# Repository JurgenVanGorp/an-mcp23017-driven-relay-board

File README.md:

Guide creation date: 13-Nov-2021

# An MCP23017 driven relay board for Home Assistant on a Raspberry Pi
A schematic and hardware board for an MCP23017 multi-I/O controller driven relays.

Previous topic: [Step 4: Controlling the MCP23017 from within Home-Assistant.](https://github.com/JurgenVanGorp/MCP23017-multi-I-O-Control-with-Raspberry-Pi-and-Home-Assistant)

## Introduction

In the previous topics it was shown how an MCP23017 can be used for controlling toggle relays with an MCP23017 multi-I/O chip. The examples made use of an MCP23017 chip on a breadboard. For real life usage we will need a PCB that can be properly installed in a rack.

This guide describes a simple PCB board in Eurocard format (10cm x 16cm) that allows connecting an MCP23017 to a Raspberry Pi with Home Assistant, over the I2C bus. The board has 15 open ended relays. The 16th output is used to drive an "identification" LED. It can be used to identify the board if you are using multiple boards, and for verification that the communication is working properly.

The board needs a 12V power supply. The 12V is converted to 5V on the board, and is also used to power the mini relays. With some modifications you can also use the board with 5V directly, but you would need to replace the relays with pin-compatible 5V relays. I am using 12V for the simple reason that all switches in my house operate on 12V. The translation to higher voltages is only done in the power box.

**WARNING** Even though the PCB board described below does provide you with physical segregation with relays, IT IS NOT SUITED FOR HIGH VOLTAGE OR HIGH CURRENT USE. The low voltage and high voltage lines on the PCB are not sufficiently separated on the PCB for safe use with high voltages. The board can be used with low-voltage (max 48V) toggle relays (aka teleruptors) at a maximum of 500 milliAmps.

## Using and changing the files in this repository

I have created the schematic and PCB in this repository with the open and free [KiCad EDA](https://www.kicad.org/) software. I cannot express enough how much I am grateful to [the developers](https://www.kicad.org/about/kicad/) of this PCB software. As far as I'm concerned the times of too-expensive PCB software are over.

The PCB file looks as follows.

The GERBER PCB Files are included in the package, so you don't need to compile these for yourself.

There are many companies that will be able to create the PCB files for you. My personal favorite is [Eurocircuits.eu](https://www.eurocircuits.com/), but that's a personal choice of course. You can also create your own PCBs; the PDF file is added in the repository. But let's be honest, ordering the PCB looks a lot more professional and will last longer.

**INFO** In honnesty: the image above does not fully match the PCB you can find in the repository. In this prototype I made use of RJ10 connectors for the I2C connections, but these connectors are difficult to find. If you find one, it will probably have a slightly footprint. For that reason I used 'standard' 3-pin connectors in the final PCB layout.

## Components used.

This is the list of components used, and where I have found them.

| Quantity | Component    | Value                     | Source                 | ~cost/Piece   |
|:--------:|--------------|--------------------------:|------------------------|--------------:|
| 1        | PCB Board    | See Gerber files | [eurocircuits.eu](https://www.eurocircuits.eu) | € 35.00 | 
| 1        | IC           | MCP23017                  | [mouser.com](https://eu.mouser.com/ProductDetail/Microchip/MCP23017-E-SP?qs=sGAEpiMZZMsVgcksf1EMUq%252Bl%252ByrW%252Br2s) | € 1.35 |
| 2        | 14 pins socket | MCP23017                  | [mouser.com](https://www.conrad.com/p/tru-components-ic-socket-contact-spacing-254-mm-762-mm-number-of-pins-14-1-pcs-1568704) | € 0.40 |
| 2        | Resistor     | 470 |  |  | 
| 16       | Diode        | 1N4007 | [conrad.com](https://www.conrad.com/p/diotec-si-rectifier-1n4007-do-204al-1000-v-1-a-162272) | € 0.09 | 
| 15       | Resistor     | 4K7 | [conrad.com](https://www.conrad.com/p/tru-components-tc-mf0w4ff4701a50203-metal-film-resistor-47-k-axial-lead-0207-025-w-1-1-pcs-1585059) | € 0.10 | 
| 1        | Capacitor    | 22nF  | [conrad.com](https://www.conrad.com/p/tru-components-tc-k22nf5-ceramic-capacitor-tht-22-nf-100-v-20-1-pcs-1589451) | € 0.10 | 
| 3        | Capacitor    | 220nF | [conrad.com](https://www.conrad.com/p/kemet-c320c224m5u5ta-ceramic-capacitor-radial-lead-220-nf-50-v-20-l-x-w-x-h-508-x-318-x-584-mm-1-pcs-1420328) | € 0.60 | 
| 2        | Capacitor     | 220uF | [conrad.com](https://www.conrad.com/p/europe-chemicon-eky-500ell221mj16s-electrolytic-capacitor-radial-lead-5-mm-220-f-50-v-20-x-h-10-mm-x-16-mm-1-pc-1505568) | € 0.50 | 
| 15       | Transistor   | BC547 **(1)** | [conrad.com](https://www.conrad.com/search?search=140539&searchType=regular) | € 0.05 |
| 1        | 12V to 5V DC | OKI-78SR-5_1.5-W36H-C **(2)** | [mouser.com](https://eu.mouser.com/ProductDetail/Murata/OKI-78SR-5-15-W36H-C?qs=sGAEpiMZZMsbRVlHDoeFZD%252BySXGErvIJc3su7QBo1Is%3D) | € 3.64 | 
| 15       | Relay 12V    | G5V-1-DC12 **(3)**           | [mouser.com](https://eu.mouser.com/ProductDetail/Omron/G5V-1-DC12?qs=sGAEpiMZZMv0NwlthflBi%2Fae0vpIDW5L) | € 1.45 |
| 3        | Jumper       | N/A      | e.g. [conrad.com](https://www.conrad.com/p/tru-components-shorting-jumper-contact-spacing-254-mm-pins-per-row2-content-100-pcs-1693950) | € 0.35 | 
| 1        | Connector 1x2 | DG350-3.5-03P    | [conrad.com](https://www.conrad.com/p/degson-dg350-35-02p-14-00ah-200-screw-terminal-2-mm-number-of-pins-2-green-200-pcs-1595136) | € 0.22 | 
| 2        | Connector 1x3 | DG350-3.5-02P    | [conrad.com](https://www.conrad.com/p/degson-dg350-35-03p-14-00ah-200-screw-terminal-2-mm-number-of-pins-3-green-200-pcs-1595217) | € 0.32 | 
| 5        | 1x6 Spring connector | PTR 54191060051E | [conrad.com](https://www.conrad.com/p/ptr-54191060051e-spring-loaded-terminal-075-mm-number-of-pins-6-pebble-grey-1-pcs-569770) | € 0.36 | 
| 1        | LED "IDENT"  | Green 5 mm | [conrad.com](https://www.conrad.com/p/vishay-tlhr-5400-led-wired-super-red-circular-5-mm-10-mcd-30-30-ma-2-v-184389) | € 0.20 | 
| 1        | LED "POWER"  | Red 5 mm | [conrad.com](https://www.conrad.com/p/kingbright-l-7113id-led-wired-red-circular-5-mm-45-mcd-30-20-ma-2-v-180139) | € 0.20 |
| TOTAL    | | | | ~€ 74 |

**(1)** Also known as 2N3904 / BC547 / PN2222 / 2N4401 / NTE123AP. Make your pick, this is a "standard" NPN transistor. 

**(2)** The OKI-78SR is a 12V DC to 5V DC converter. It is pin-compatible with an [LM7805](https://eu.mouser.com/ProductDetail/Texas-Instruments/LM7805CT?qs=sGAEpiMZZMsFKQfwwdJx%2FxW4Tr%252BxPyoqmeSSFfZw3i4%3D). The current drawn is very low, so feel free to replace it with an LM7805 if you prefer.

**(3)** You can also power the board with 5V. In that case you will need to bridge the DC/DC converter and replace the 12V relays with the 5V [G5V-1-DC5 version](https://eu.mouser.com/ProductDetail/Omron/G5V-1-2-DC5?qs=sGAEpiMZZMsKEdP9slC0YbH1hXJZnuIH7AhUMezYhKg%3D).

The assembled board should look something like the following. Please mind that the below board is the prototype and looks slightly different from the PCB.

## Schematic decription

The overall schematic looks as follows. You can [download the shematic in PDF format here](https://github.com/JurgenVanGorp/an-mcp23017-driven-relay-board/blob/main/DOMOTICS%20MCP23017%20Relay%20Control/PCB%20Layouts.pdf).

True, this is a bit crowded, and not easy to follow. So, let's highlight a few details here. The easy part is the top left section, containing the connector block with five 6-pins spring connectors.

Then, let's have a look at one of the fifteen relay configurations you can find in the top right section of the schematic.

All fifteen relays have the same straight-forward configuration.
* The NO (Normally-Open) and CO (Common) pins of the relay are routed to the connector block. I.e. 'in rest' the outputs are not connected.
* Resistor R1 is connected to the output of one of the MCP23017 pins.
* Transistor T1 is used as a switch. Strictly spoken, any pin-compatible NPN transistor can be used here.
* Diode D1 protects the transistor when switching off the relay. Since this is a coil relay, suddenly switching off the relay can result in a reverse voltage peak which can potentially damage the transistor. Diode D1 make sure that a reverse current in the coil is shortcut.

Finally, let's look at the MCP23017 block in more detail.
* The output pins of both GPA and GPB are routed to the relay blocks. 
* GPB7 ("pin 15" in Home Assistant) is connected to the "Identification" LED D18 and can be used to identify the board and test the MCP23017 operation.
* Connectors J6 and J7 are used to connect the I2C pins to the Raspberry Pi. Remark that both connectors are configured fully parallel, so that the connectors can be used to cascade multiple boards.
* Jumpers JP1 .. JP3 are used as the address selectors.
* LED D17 is just connected to the +5V output and can be used to verify the power.

## Mounting the PCB Board

The PCBs are 10cm x 16cm which allows mounting them in a standard EuroRack, as in the image below. If you want to know more about Euroracks, [RS gives a nice overview here](https://nl.rs-online.com/web/generalDisplay.html?id=ideas-and-advice/eurocards-pcb-guide). They also sell different types of enclosures.

An alternate way for mounting the board, is a DIN rail case. The components for a DIN rail mount are e.g. the following.

| Quantity | Component                    | Description            | Source                 | ~cost/Piece   |
|:--------:|------------------------------|------------------------|------------------------|--------------:|
| 2 or 3   | Phoenix Contact UM108-FE     | DIN rail mount         | [conrad.com](https://www.conrad.com/p/phoenix-contact-um108-fe-din-rail-casing-base-1075-plastic-10-pcs-454634) | € 0.70 | 
| 1        | Phoenix Contact UM108-SEFE/R | Right side panel       | [conrad.com](https://www.conrad.com/p/phoenix-contact-um108-sefer-din-rail-casing-side-panel-plastic-10-pcs-453303) | € 1.00 |
| 1        | Phoenix Contact UM108-SEFE/R | Left side panel        | [conrad.com](https://www.conrad.com/search?search=459039&searchType=regular) | € 1.00 |
| 1        | Phoenix Contact UM100-PROFIL 100CM | back plate (1m)  | [conrad.com](https://www.conrad.com/p/phoenix-contact-um100-profil-100cm-din-rail-casing-plastic-1-pcs-456207) | € 30.00 |

Next topic: [A sensor (relay) board for sensing 240V high power states with an MCP23017.](https://github.com/JurgenVanGorp/an-MCP23017-driven-high-voltage-sensor-board)

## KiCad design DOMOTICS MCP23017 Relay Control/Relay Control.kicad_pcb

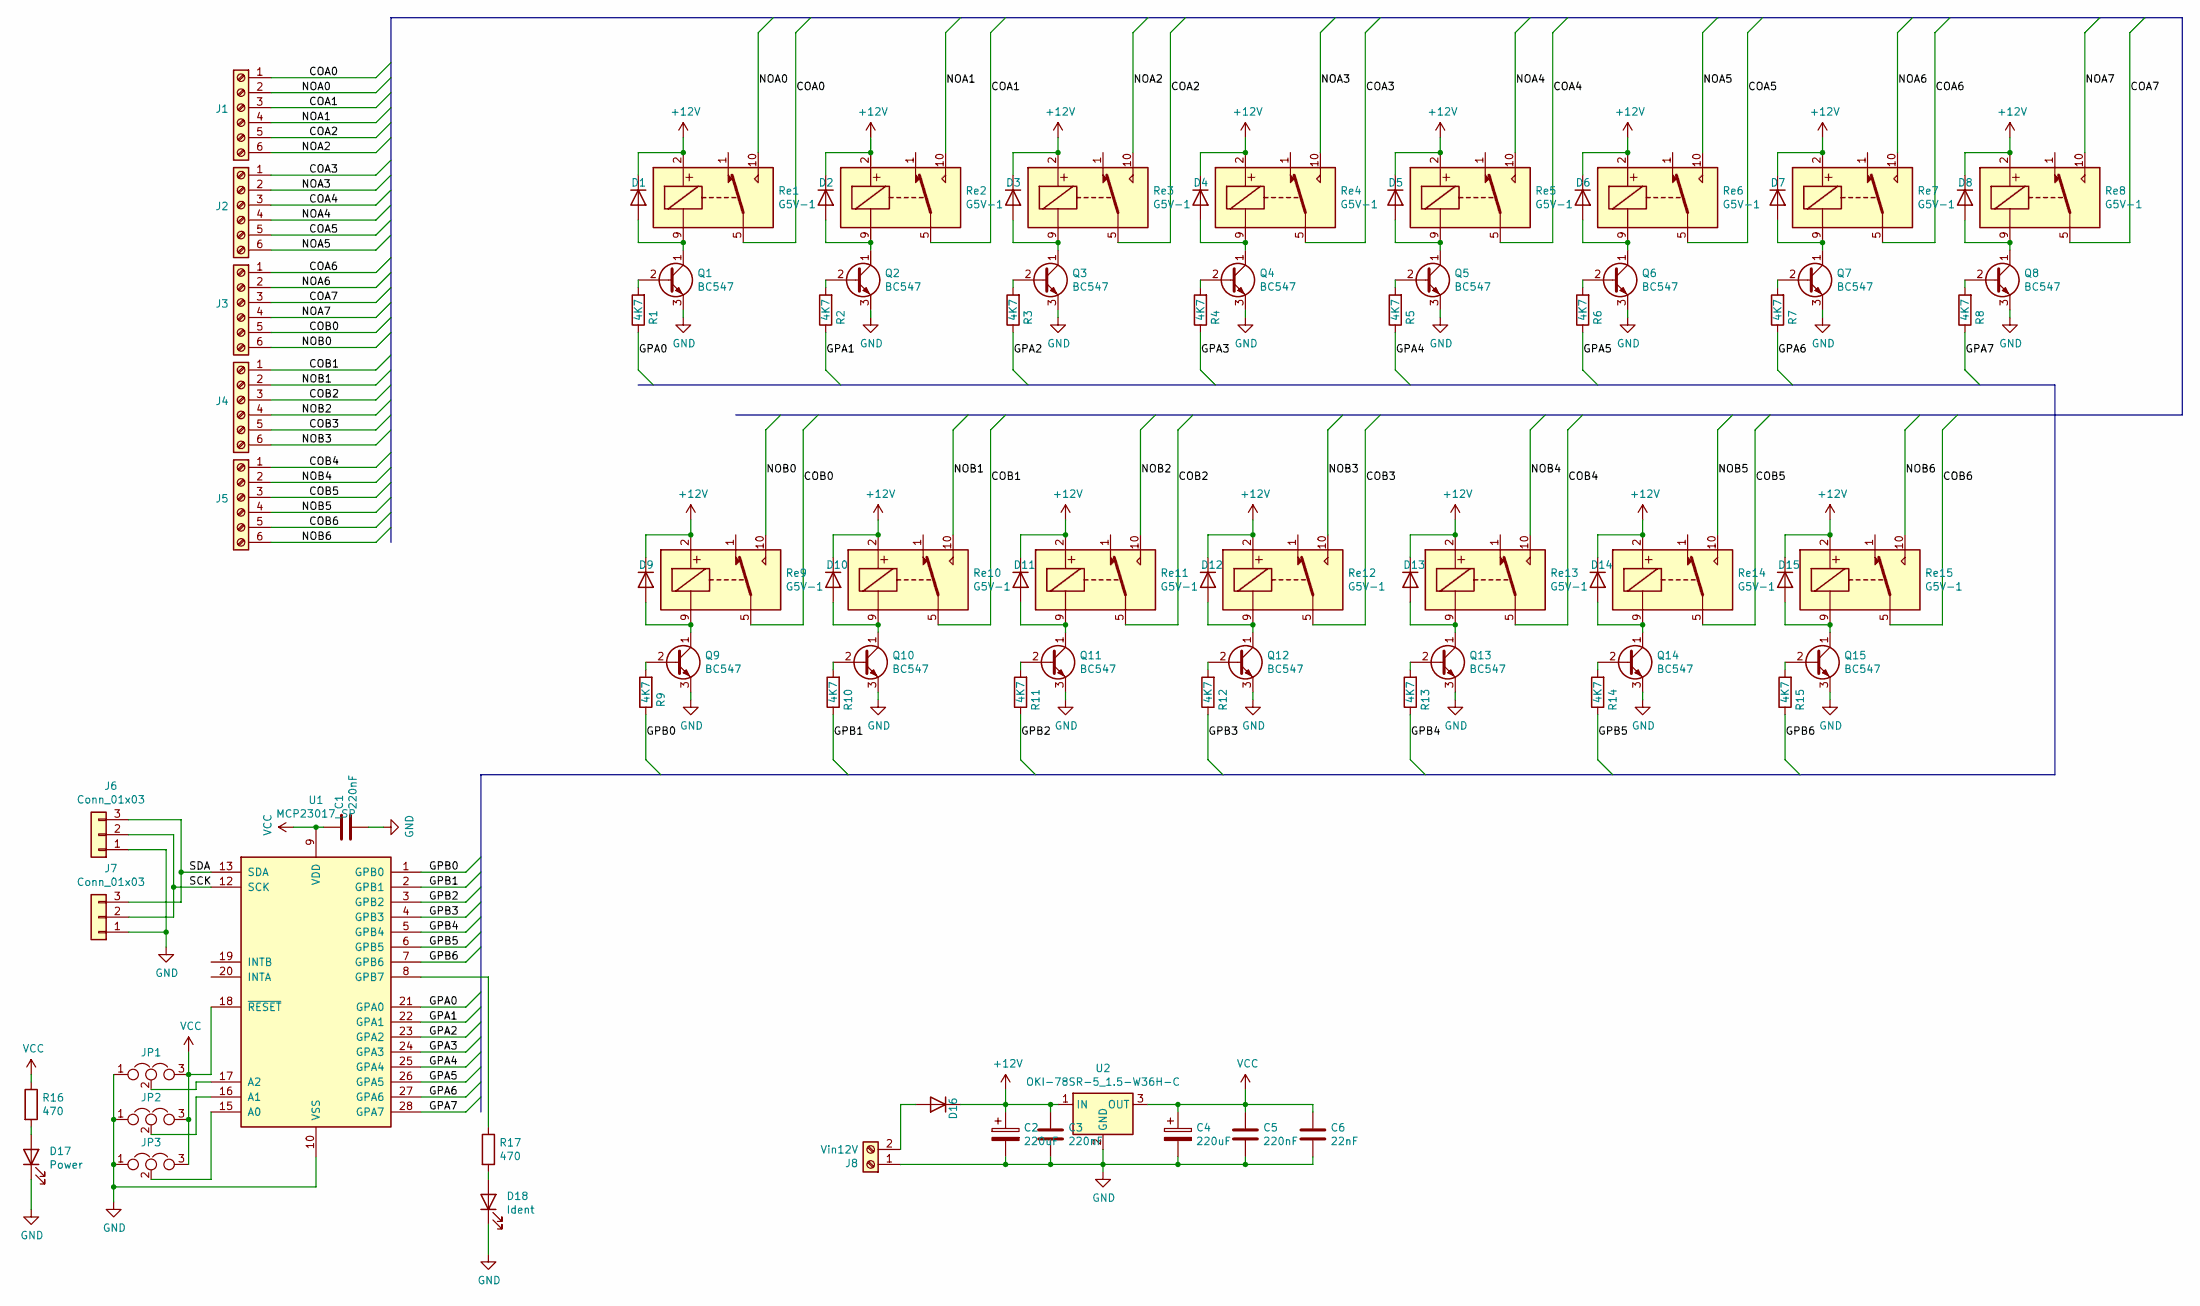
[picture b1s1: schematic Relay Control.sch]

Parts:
C1, C3, C5: 220nF; Capacitor
C2, C4: 220uF; CP_Radial_D8.0mm_P5.00mm
C6: 22nF; Capacitor
D1, D2, D3, D4, D5, D6, D7, D8, D9, D10, D11, D12, D13, D14, D15, D16: 1N4007; Diode10.16mm_Horizontal_Jurgen
D17: Power; LED_Radial_D6.3mm_P2.50mm_Jurgen
D18: Ident; LED_Radial_D6.3mm_P2.50mm_Jurgen
J1, J2, J3, J4, J5: Screw_Terminal_01x06; Connector_1x6_ZigZag
J6, J7: Conn_01x03; Connector_1x3_Normal
J8: Vin12V; TerminalBlock_bornier-2_P5.08mm_jurgen
JP1: A2; Connector_1x3_Normal
JP2: A1; Connector_1x3_Normal
JP3: A0; Connector_1x3_Normal
Q1, Q2, Q3, Q4, Q5, Q6, Q7, Q8, Q9, Q10, Q11, Q12, Q13, Q14, Q15: BC547; TO-92_Inline_Wide_Jurgen
R1, R2, R3, R4, R5, R6, R7, R8, R9, R10, R11, R12, R13, R14, R15: 4K7; R_Radial
R16, R17: 470; R_Radial
Re1, Re2, Re3, Re4, Re5, Re6, Re7, Re8, Re9, Re10, Re11, Re12, Re13, Re14, Re15: G5V-1; Relais_SPDT_Omron_G5V-1
U1: MCP23017_SP; DIP-28_W7.62mm
U2: OKI-78SR-5_1.5-W36H-C; Converter_DCDC_muRata_OKI-78SR_Horizontal

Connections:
+12V: C2.1, C3.1, D1.1 (K), D2.1 (K), D3.1 (K), D4.1 (K), D5.1 (K), D6.1 (K), D7.1 (K), D8.1 (K), D9.1 (K), D10.1 (K), D11.1 (K), D12.1 (K), D13.1 (K), D14.1 (K), D15.1 (K), D16.1 (K), Re1.2, Re2.2, Re3.2, Re4.2, Re5.2, Re6.2, Re7.2, Re8.2, Re9.2, Re10.2, Re11.2, Re12.2, Re13.2, Re14.2, Re15.2, U2.1 (IN)
/COA0: J1.1, Re1.5, Re1.6
/COA1: J1.3, Re2.5, Re2.6
/COA2: J1.5, Re3.5, Re3.6
/COA3: J2.1, Re4.5, Re4.6
/COA4: J2.3, Re5.5, Re5.6
/COA5: J2.5, Re6.5, Re6.6
/COA6: J3.1, Re7.5, Re7.6
/COA7: J3.3, Re8.5, Re8.6
/COB0: J3.5, Re9.5, Re9.6
/COB1: J4.1, Re10.5, Re10.6
/COB2: J4.3, Re11.5, Re11.6
/COB3: J4.5, Re12.5, Re12.6
/COB4: J5.1, Re13.5, Re13.6
/COB5: J5.3, Re14.5, Re14.6
/COB6: J5.5, Re15.5, Re15.6
/GPA0: R1.1, U1.21 (GPA0)
/GPA1: R2.1, U1.22 (GPA1)
/GPA2: R3.1, U1.23 (GPA2)
/GPA3: R4.1, U1.24 (GPA3)
/GPA4: R5.1, U1.25 (GPA4)
/GPA5: R6.1, U1.26 (GPA5)
/GPA6: R7.1, U1.27 (GPA6)
/GPA7: R8.1, U1.28 (GPA7)
/GPB0: R9.1, U1.1 (GPB0)
/GPB1: R10.1, U1.2 (GPB1)
/GPB2: R11.1, U1.3 (GPB2)
/GPB3: R12.1, U1.4 (GPB3)
/GPB4: R13.1, U1.5 (GPB4)
/GPB5: R14.1, U1.6 (GPB5)
/GPB6: R15.1, U1.7 (GPB6)
/NOA0: J1.2, Re1.10
/NOA1: J1.4, Re2.10
/NOA2: J1.6, Re3.10
/NOA3: J2.2, Re4.10
/NOA4: J2.4, Re5.10
/NOA5: J2.6, Re6.10
/NOA6: J3.2, Re7.10
/NOA7: J3.4, Re8.10
/NOB0: J3.6, Re9.10
/NOB1: J4.2, Re10.10
/NOB2: J4.4, Re11.10
/NOB3: J4.6, Re12.10
/NOB4: J5.2, Re13.10
/NOB5: J5.4, Re14.10
/NOB6: J5.6, Re15.10
/SCK: J6.2, J7.2, U1.12 (SCK)
/SDA: J6.3, J7.3, U1.13 (SDA)
GND: C1.2, C2.2, C3.2, C4.2, C5.2, C6.2, D17.1 (K), D18.1 (K), J6.1, J7.1, J8.1, JP1.1, JP2.1, JP3.1, Q1.3 (E), Q2.3 (E), Q3.3 (E), Q4.3 (E), Q5.3 (E), Q6.3 (E), Q7.3 (E), Q8.3 (E), Q9.3 (E), Q10.3 (E), Q11.3 (E), Q12.3 (E), Q13.3 (E), Q14.3 (E), Q15.3 (E), U1.10 (VSS), U2.2 (GND)
unnamed: D1.2 (A), Q1.1 (C), Re1.9
unnamed: D2.2 (A), Q2.1 (C), Re2.9
unnamed: D3.2 (A), Q3.1 (C), Re3.9
unnamed: D4.2 (A), Q4.1 (C), Re4.9
unnamed: D5.2 (A), Q5.1 (C), Re5.9
unnamed: D6.2 (A), Q6.1 (C), Re6.9
unnamed: D7.2 (A), Q7.1 (C), Re7.9
unnamed: D8.2 (A), Q8.1 (C), Re8.9
unnamed: D9.2 (A), Q9.1 (C), Re9.9
unnamed: D10.2 (A), Q10.1 (C), Re10.9
unnamed: D11.2 (A), Q11.1 (C), Re11.9
unnamed: D12.2 (A), Q12.1 (C), Re12.9
unnamed: D13.2 (A), Q13.1 (C), Re13.9
unnamed: D14.2 (A), Q14.1 (C), Re14.9
unnamed: D15.2 (A), Q15.1 (C), Re15.9
unnamed: D16.2 (A), J8.2
unnamed: D17.2 (A), R16.2
unnamed: D18.2 (A), R17.2
unnamed: JP1.2, U1.17 (A2)
unnamed: JP2.2, U1.16 (A1)
unnamed: JP3.2, U1.15 (A0)
unnamed: Q1.2 (B), R1.2
unnamed: Q2.2 (B), R2.2
unnamed: Q3.2 (B), R3.2
unnamed: Q4.2 (B), R4.2
unnamed: Q5.2 (B), R5.2
unnamed: Q6.2 (B), R6.2
unnamed: Q7.2 (B), R7.2
unnamed: Q8.2 (B), R8.2
unnamed: Q9.2 (B), R9.2
unnamed: Q10.2 (B), R10.2
unnamed: Q11.2 (B), R11.2
unnamed: Q12.2 (B), R12.2
unnamed: Q13.2 (B), R13.2
unnamed: Q14.2 (B), R14.2
unnamed: Q15.2 (B), R15.2
unnamed: R17.1, U1.8 (GPB7)
VCC: C1.1, C4.1, C5.1, C6.1, JP1.3, JP2.3, JP3.3, R16.1, U1.9 (VDD), U1.18 (~RESET~), U2.3 (OUT)

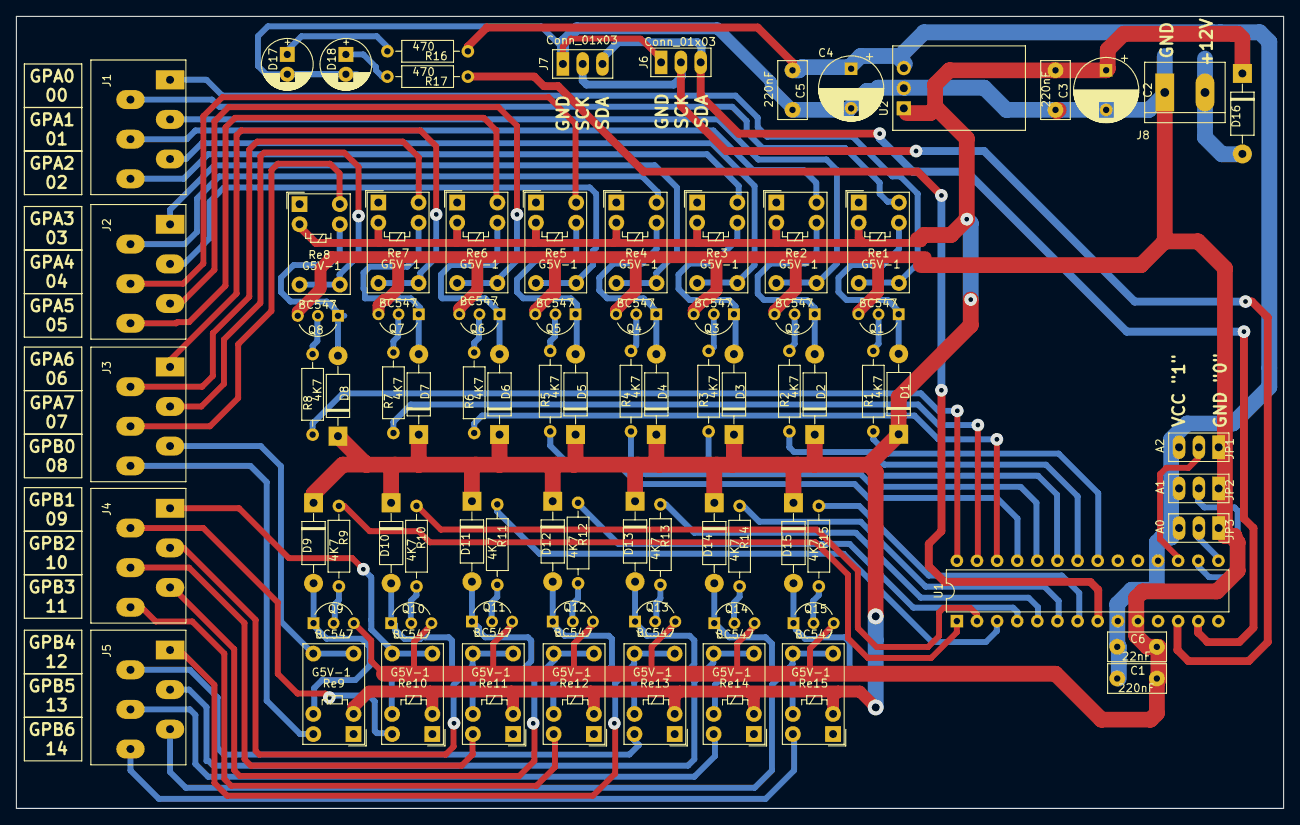
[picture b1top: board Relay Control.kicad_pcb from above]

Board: 2 copper layers, 160.0 x 100.0 mm, 84 parts (0 on the bottom side), 87 nets.

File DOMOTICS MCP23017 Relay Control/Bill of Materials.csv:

"Id";"Designator";"Package";"Quantity";"Designation";"Supplier and ref";
1;"U1";"DIP-28_W7.62mm";1;"MCP23017_SP";;;
2;"U2";"Converter_DCDC_muRata_OKI-78SR_Horizontal";1;"OKI-78SR-5_1.5-W36H-C";;;
3;"Re15,Re14,Re13,Re12,Re11,Re10,Re9,Re8,Re7,Re6,Re5,Re4,Re3,Re2,Re1";"Relais_SPDT_Omron_G5V-1";15;"G5V-1";;;
4;"R17,R16";"R_Radial";2;"470";;;
5;"R15,R14,R13,R12,R11,R10,R9,R8,R7,R6,R5,R4,R3,R2,R1";"R_Radial";15;"4K7";;;
6;"Q15,Q14,Q13,Q12,Q11,Q10,Q9,Q8,Q7,Q6,Q5,Q4,Q3,Q2,Q1";"TO-92_Inline_Wide_Jurgen";15;"BC547";;;
7;"JP3";"Connector_1x3_Normal";1;"A0";;;
8;"JP2";"Connector_1x3_Normal";1;"A1";;;
9;"JP1";"Connector_1x3_Normal";1;"A2";;;
10;"J8";"TerminalBlock_bornier-2_P5.08mm_jurgen";1;"Vin12V";;;
11;"J7,J6";"Connector_1x3_Normal";2;"Conn_01x03";;;
12;"J5,J4,J3,J2,J1";"Connector_1x6_ZigZag";5;"Screw_Terminal_01x06";;;
13;"D18";"LED_Radial_D6.3mm_P2.50mm_Jurgen";1;"Ident";;;
14;"D17";"LED_Radial_D6.3mm_P2.50mm_Jurgen";1;"Power";;;
15;"D16,D15,D14,D13,D12,D11,D10,D9,D8,D7,D6,D5,D4,D3,D2,D1";"Diode10.16mm_Horizontal_Jurgen";16;"1N4007";;;
16;"C6";"Capacitor";1;"22nF";;;
17;"C5,C3,C1";"Capacitor";3;"220nF";;;
18;"C4,C2";"CP_Radial_D8.0mm_P5.00mm";2;"220uF";;;

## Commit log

2021-11-13 Schematics and PCB layout
2021-11-13 Images
2021-11-13 Illustrating images
2021-11-13 Initial
2021-11-13 BoM updated
2021-11-13 Detaile description in the README
2021-11-13 Detailed description in the README
